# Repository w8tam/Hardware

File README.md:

# Hardware

Use any of this at your own risk.

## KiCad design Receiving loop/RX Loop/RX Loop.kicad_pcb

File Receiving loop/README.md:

I'm not trained to design this stuff, so use it at your own risk.
It works for me, it may not work for you.  73 de w8tam

Build notes for Loop Amplifier:

If you're not concerned about the front end of the GALI-74s, you
can skip placing the relays and just short the loop connection
through.

The values for R2/R3 are adjustable. I'm using 53.6ohm, but 51ohm
is close enough. Look at the GALI-74 datasheet to figure out what
resistor you need, for what voltage your U1 regulator is. I went
with 9v, which means 50'ish ohms to get the voltage right.

My goal is to use 75 ohm feedline, so I put in the 1.5:1 balun T1
using a Fair-Rite 2873000202 turns are marked on the board. Short
past it if you want to use 50ohms. I haven't tried that.

All capacitors should be rated higher than max voltage. I went with
25v and 35v to have plenty of headroom.

Match R1 & R5 and R6 & R7. Values aren't critical, but matching is.
Pick two that are very close in value.

Physical contruction of the loop:

I designed this board to fit into a Carlon E983FR-CAR Type T Conduit
Body.

I used 10' of 3/4" Pex-Al-Pex, and used some heatshrink to fill the
gap between the OD of the 3/4" Pex-Al-Pex and the ID of a 1" stub
of PVC water pipe. The 1" PVC fits into the Carlon box end. I froze
the Pex-Al-Pex with heatshrink on it, and hit the PVC with a heat
gun and they slid together nicely, then have a pressure fit. I don't
trust this to be water tight, so I am going to weather seal it. The
whole thing will get painted with UV protectant paint.

Bias Tee with PTT bypass:

I'm still working on this circuit, but I'm pretty close.

The idea will be that when powered up, it will use 6v PTT signal
(from my W2IHY) to keep the relay closed providing 13.8v bias voltage
on the feedline to the loop. When I trip PTT, it will remove the
bias voltage, causing the loop to ground itsself when I transmit.

This bias tee board will be designed to fit many needs, 50 or 75
ohms input/output, and can have a PTT connection or not. I'm
designing it to fit into a Hammond 1455C801.

I'm not trained to design this stuff, so use it at your own risk.
73 de w8tam

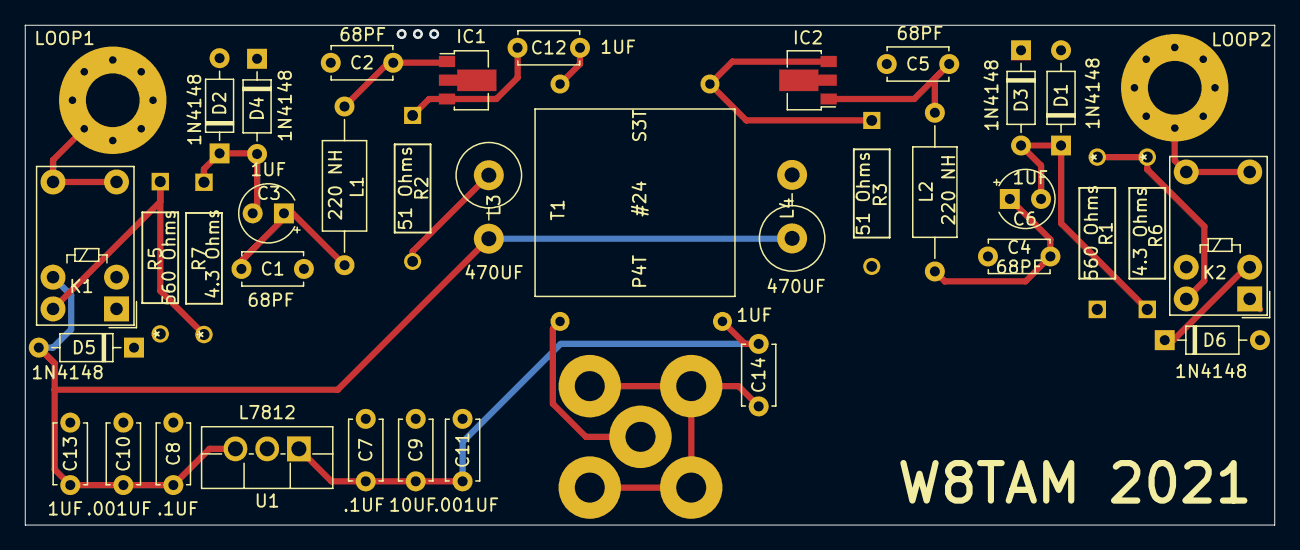
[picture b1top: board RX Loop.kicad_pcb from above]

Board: 2 copper layers, 100.0 x 40.0 mm, 39 parts (1 on the bottom side), 19 nets.

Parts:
ANT1: MountingHole_Pad; MountingHole_4.3mm_M4_Pad_Via
C1, C2, C4, C5: 68PF; C_Disc_D4.7mm_W2.5mm_P5.00mm
C3, C6: 1UF; CP_Radial_Tantal_D4.5mm_P2.50mm
C7, C8: .1UF; C_Disc_D4.7mm_W2.5mm_P5.00mm
C9: 10UF; C_Disc_D4.7mm_W2.5mm_P5.00mm
C10, C11: .001UF; C_Disc_D4.7mm_W2.5mm_P5.00mm
C12, C13, C14: 1UF; C_Disc_D4.7mm_W2.5mm_P5.00mm
D1, D2, D3, D4, D5, D6: 1N4148; D_DO-35_SOD27_P7.62mm_Horizontal
IC1, IC2: GALI-74; SOT-89-3
J1: VCC; Fconnector
K1, K2: G5V-1; Relay_SPDT_Omron_G5V-1
L1, L2: 220 NH; L_Axial_L7.0mm_D3.3mm_P12.70mm_Horizontal_Fastron_MICC
L3, L4: 470UF; Choke-Vertical
LOOP2: MountingHole_Pad; MountingHole_4.3mm_M4_Pad_Via
R1, R5: 560 Ohms; RNF14FTD1K00
R2, R3: 51 Ohms; Resistor
R6, R7: 4.3 Ohms; RNF14FTD1K00
T1: P4T #24 S3T; Binocular
U1: L7812; TO-220F-3_Vertical

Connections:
/P1: C12.1, T1.1
GND: C1.2, C2.2, C4.2, C5.2, C7.2, C8.2, C9.2, C10.2, C11.2, C13.2, C14.1, D1.2, D2.2, D3.1, D4.1, D5.1, D6.2, IC1.2, IC2.2, J1.2, K1.1, K2.1, K2.9, R1.1, R5.2, U1.2
unnamed: ANT1.1, K1.5, K1.6
unnamed: K2.5, K2.6, LOOP2.1
unnamed: C1.1, C3.1, L1.1
unnamed: C2.1, IC1.1, L1.2
unnamed: C3.2, D2.1, D4.2, R7.1
unnamed: C4.1, C6.1, L2.1
unnamed: C5.1, IC2.1, L2.2
unnamed: C6.2, D1.1, D3.2, R6.1
unnamed: C8.1, C10.1, C13.1, D5.2, D6.1, K1.9, K2.2, L3.1, L4.2, U1.3
unnamed: C7.1, C9.1, C11.1, C14.2, T1.4, U1.1
unnamed: C12.2, IC1.3, R2.1
unnamed: IC2.3, R3.1, T1.2
unnamed: J1.1, T1.3
unnamed: K1.10, R5.1, R7.2
unnamed: K2.10, R1.2, R6.2
unnamed: L3.2, R2.2
unnamed: L4.1, R3.2

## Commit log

2021-06-05 Adding previous work.
2021-06-08 Fixed footprint label for U1
2021-06-08 .DS_Store banished!
2021-06-08 Updated PCB
2021-06-20 Updating changes. Cleaning up repo.wq
2021-06-20 Added readme.
2021-06-20 Updated readme.
2021-06-20 Cleaned up. Added latest revisions.
2021-06-20 Merged changes.
2021-06-20 Merged changes. Updated metadata.
2021-06-20 Updated schematic.
2023-02-02 Panel PCB I made for my Tahoe

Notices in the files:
parts and their libraries:
Copyright 2016 Accelerated Designs. All rights reserved.
